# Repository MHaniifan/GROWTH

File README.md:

## GROWTH: Greenhouse Remote Operations With Temperature & Humidity

<div align="justify">
    Proyek ini bertujuan untuk mengembangkan sistem automasi cerdas berbasis Mikrokontroler AVR untuk Smart Farming, menggunakan komponen utama seperti Arduino Mega, sensor YL-69 dan DHT-11, serta pompa air dan kipas. Arduino Mega bertindak sebagai mikrokontroler utama yang mengontrol komunikasi antar sensor dan aktuator, memungkinkan pemantauan dan pengontrolan secara real-time. Sistem ini menggunakan Timer pada AVR untuk menjaga sinkronisasi waktu, dan Interrupt untuk menyalakan Pompa Air ketika kelembaban dibawah batas.
</div>

<div align="justify">
    Pompa Air akan menyala setiap jadwal penyiraman yang sudah ditentukan. Dimana jadwal penyiraman dan lama pompa menyala, diatur pada GUI pada Komputer yang terhubung ke Mikrokontroler menggunakan komunikasi UART. Untuk Kipas akan menyala setiap suhu telah melewati batas yang ditentukan, dimana batas suhunya dapat diatur pada GUI.
</div>

<div align="justify">
    Dengan menggunakan UART, seluruh data dari sensor-sensor ini dikirimkan ke Komputer. Memungkinkan petani untuk memantau penggunaan energi dan kondisi lingkungan secara langsung dari Komputer. Sistem ini dirancang untuk meningkatkan efisiensi energi, hasil produksi, serta dapat mengurangi kerugian dengan mengotomatiskan berbagai fungsi dan memberikan kendali yang lebih fleksibel.
</div>

## Supported By :
>- Dosen Pengampu : Akhmad Hendriawan ST., MT. (NIP.197501272002121003)
>- Mata kuliah : Mikrokontroler
>- Program Studi : Sarjana Terapan Teknik Elektronika
>- Politeknik Elektronika Negeri Surabaya<br> 

## Team Member :
|      NRP      |       Nama      |    Jobdesk    |   Github |
| :-----------:|:----------------:| :------------:| :-----:|
| 2123600007    | Muhammad Haniifan  | Project Manager       | [Haniifan](https://github.com/MHaniifan)
| 2123600011    | Monalisa Br. Sidauruk         |   Hardware Specialist | [Lisa](https://github.com/MonalisaSidauruk)
| 2123600015    | Fakhrihans Ardiyanto         |    UI/UX Designer      | [Rihan](https://github.com/FakhrihansArdiyanto)
| 2123600027    | Darda Drestanala                | 3D Designer | [Darda](https://github.com/dardadrestanala)
| 2123600029    | Aurora Putri Salsabillah Rofii               | PCB Designer     | [Aurora](https://github.com/aurorapsr)
| 2124640016    | Arif Ramadhan               | Programmer     |[Arif](https://github.com/arif-rmdhn)

##

## Daftar Isi
- [Deskripsi Project](https://github.com/MHaniifan/GROWTH#growth-greenhouse-remote-operations-with-temperaturehumidity)
- [Team Member](https://github.com/MHaniifan/GROWTH#team-member-)
- [Keunggulan](https://github.com/MHaniifan/GROWTH#keunggulan)
- [Desain Hardware](https://github.com/MHaniifan/GROWTH#desain-hardware)
- [Printed Circuit Board](https://github.com/MHaniifan/GROWTH#printed-circuit-board-pcb)
- [Program](https://github.com/MHaniifan/GROWTH#program)
- [Tampilan UI/UX](https://github.com/MHaniifan/GROWTH#tampilan-uiux)

## Keunggulan
- **Pemantauan Real-Time**: Mengukur perubahan kelembaban dan suhu dengan sensor secara terus - menerus.
- **Efisiensi dan Penghematan Biaya**: Mengurangi penggunaan listrik karena pompa dan kipas hanya dinyalakan ketika melewati batas normal tanaman.
- **Kendali Otomatis**: Menggunakan sensor untuk mengamati perubahan kondisi dan relay untuk mengaktifkan pompa dan kipas sehingga tidak dikontrol oleh manusia.
- **Meningkatkan Hasil Panen**: Mencegah tanaman kekeringan dan kepanasan sehingga dapat meningkatkan kondisi tanaman.

## Desain Hardware
Blok Diagram

Wiring Diagram

## Printed Circuit Board (PCB)
Skematik PCB

Desain PCB

## Desain 3D

## Flowchart Program

## Tampilan UI/UX

## Pengembangan Kedepannya
- Penambahan IoT untuk Pemantauan Jarak Jauh
- Penambahan RTC untuk Penjadwalan Penyiraman
- Penambahan Desain Casing yang Tahan Air
- Penambahan Baterai untuk Supply Darurat

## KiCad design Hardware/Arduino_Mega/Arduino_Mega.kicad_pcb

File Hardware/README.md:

## Desain Hardware
Blok Diagram

Wiring Diagram

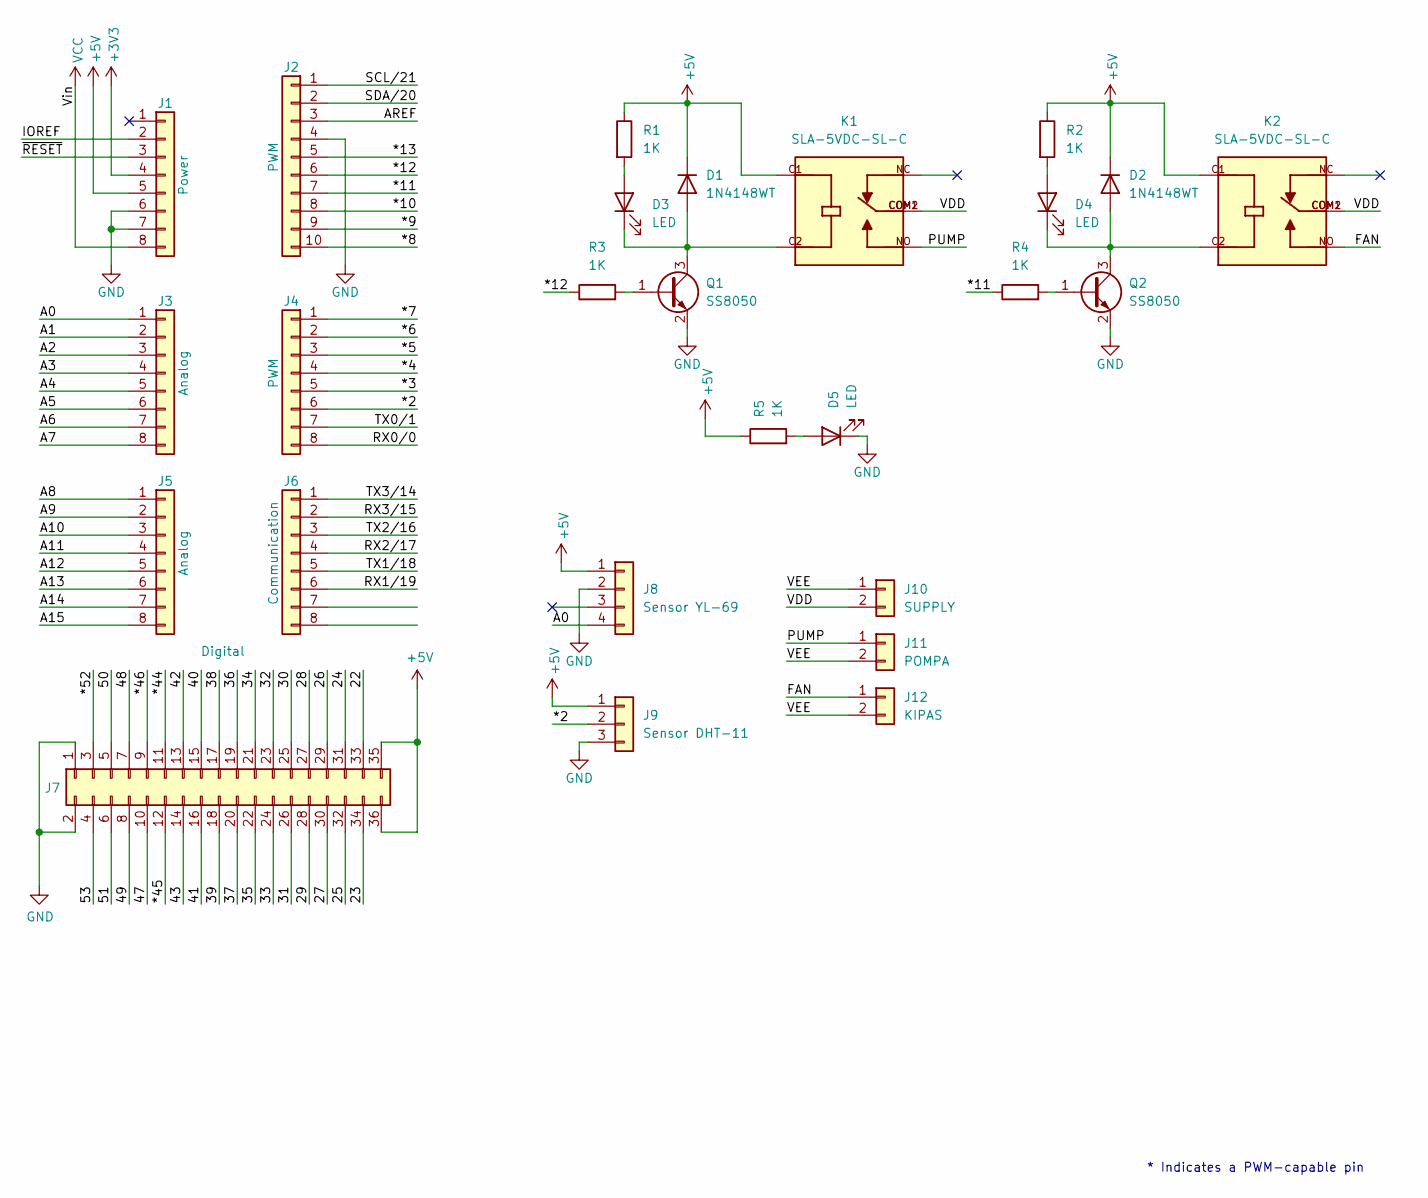
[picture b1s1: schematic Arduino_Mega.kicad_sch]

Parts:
D1, D2: 1N4148WT; D_SOD-523
D3, D4, D5: LED; LED_1206_3216Metric_Pad1.42x1.75mm_HandSolder
J1: Power; PinSocket_1x08_P2.54mm_Vertical
J2: PWM; PinSocket_1x10_P2.54mm_Vertical
J3, J5: Analog; PinSocket_1x08_P2.54mm_Vertical
J4: PWM; PinSocket_1x08_P2.54mm_Vertical
J6: Communication; PinSocket_1x08_P2.54mm_Vertical
J7: Digital; PinSocket_2x18_P2.54mm_Vertical
J8: Sensor YL-69; JST_XH_B4B-XH-A_1x04_P2.50mm_Vertical
J9: Sensor DHT-11; JST_XH_B3B-XH-A_1x03_P2.50mm_Vertical
J10: SUPPLY; TerminalBlock_Phoenix_MKDS-1,5-2-5.08_1x02_P5.08mm_Horizont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
J11: POMPA; TerminalBlock_Phoenix_MKDS-1,5-2-5.08_1x02_P5.08mm_Horizont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
J12: KIPAS; TerminalBlock_Phoenix_MKDS-1,5-2-5.08_1x02_P5.08mm_Horizont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
K1, K2: SLA-5VDC-SL-C; RELAY_SLA-12VDC-SL-C
Q1, Q2: SS8050; SOT-23
R1, R2, R3, R4, R5: 1K; R_0805_2012Metric_Pad1.20x1.40mm_HandSolder

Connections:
+3V3: J1.4
+5V: D1.1 (K), D2.1 (K), J1.5, J7.35, J7.36, J8.1, J9.1, K1.C1, K2.C1, R1.1, R2.1, R5.1
/22: J7.33
/23: J7.34
/24: J7.31
/25: J7.32
/26: J7.29
/27: J7.30
/28: J7.27
/29: J7.28
/30: J7.25
/31: J7.26
/32: J7.23
/33: J7.24
/34: J7.21
/35: J7.22
/36: J7.19
/37: J7.20
/38: J7.17
/39: J7.18
/40: J7.15
/41: J7.16
/42: J7.13
/43: J7.14
/47: J7.10
/48: J7.7
/49: J7.8
/50: J7.5
/51: J7.6
/53: J7.4
/*2: J4.6, J9.2
/*3: J4.5
/*4: J4.4
/*5: J4.3
/*6: J4.2
/*7: J4.1
/*8: J2.10
/*9: J2.9
/*10: J2.8
/*11: J2.7, R4.1
/*12: J2.6, R3.1
/*13: J2.5
/*44: J7.11
/*45: J7.12
/*46: J7.9
/*52: J7.3
/A0: J3.1, J8.4
/A1: J3.2
/A2: J3.3
/A3: J3.4
/A4: J3.5
/A5: J3.6
/A6: J3.7
/A7: J3.8
/A8: J5.1
/A9: J5.2
/A10: J5.3
/A11: J5.4
/A12: J5.5
/A13: J5.6
/A14: J5.7
/A15: J5.8
/AREF: J2.3
/FAN: J12.1, K2.NO
/IOREF: J1.2
/PUMP: J11.1, K1.NO
/RX0/0: J4.8
/RX1/19: J6.6
/RX2/17: J6.4
/RX3/15: J6.2
/SCL/21: J2.1
/SDA/20: J2.2
/TX0/1: J4.7
/TX1/18: J6.5
/TX2/16: J6.3
/TX3/14: J6.1
/VDD: J10.2, K1.COM1, K1.COM2, K2.COM1, K2.COM2
/VEE: J10.1, J11.2, J12.2
/~RESET: J1.3
GND: D5.1 (K), J1.6, J1.7, J2.4, J7.1, J7.2, J8.2, J9.3, Q1.2 (E), Q2.2 (E)
unnamed: D1.2 (A), D3.1 (K), K1.C2, Q1.3 (C)
unnamed: D2.2 (A), D4.1 (K), K2.C2, Q2.3 (C)
unnamed: D3.2 (A), R1.2
unnamed: D4.2 (A), R2.2
unnamed: D5.2 (A), R5.2
unnamed: Q1.1 (B), R3.2
unnamed: Q2.1 (B), R4.2
VCC: J1.8

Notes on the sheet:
* Indicates a PWM-capable pin

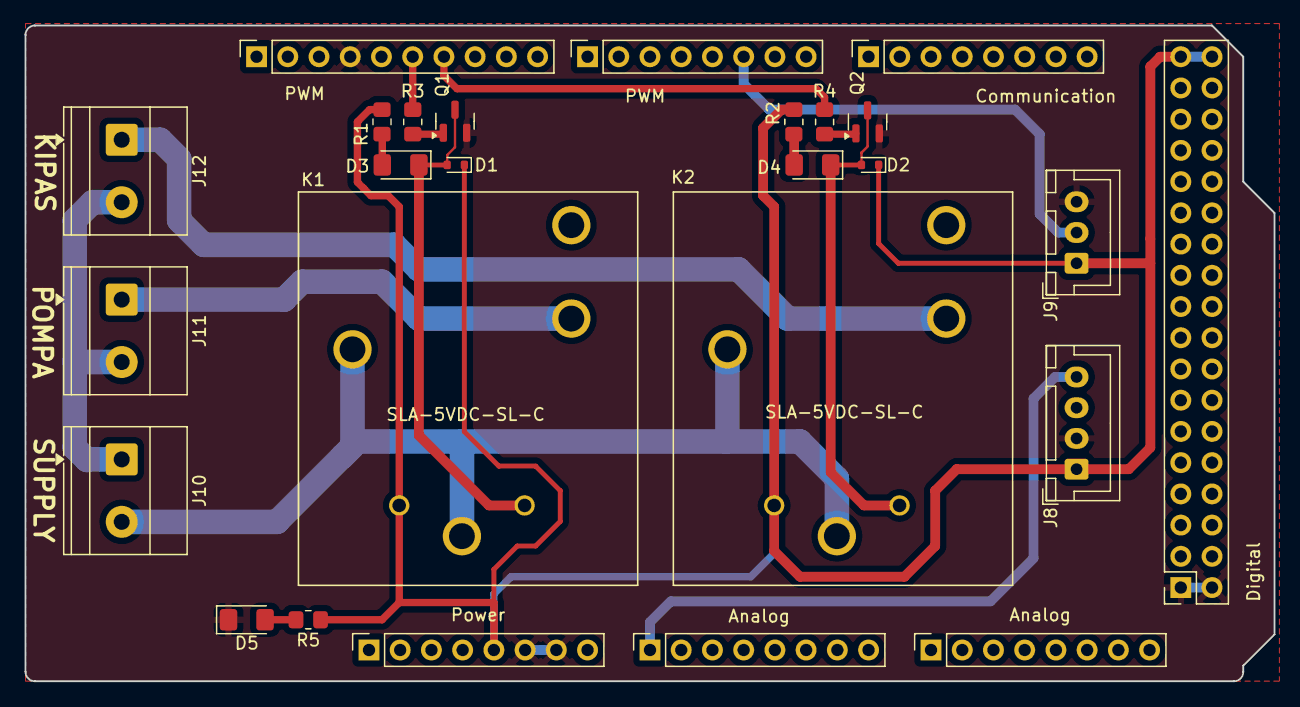
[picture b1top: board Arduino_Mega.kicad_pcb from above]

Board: 2 copper layers, 101.6 x 53.3 mm, 26 parts (0 on the bottom side), 17 nets.

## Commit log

2025-04-18 Delete
2025-04-18 Update Folder
2025-04-28 Create Assets
    Add folder
2025-04-28 Create ....
2025-04-28 Add Folder
2025-05-06 Add Files
2025-05-19 Rename Folder
2025-05-19 Create New Folder
2025-05-19 Edit Files
2025-05-20 Update Program 20/05/2025
2025-05-30 update program
2025-06-02 Add Fuxa Program
2025-06-02 Edit README.md
2025-06-02 edit main.cpp
2025-06-02 Rename Files
2025-06-02 Add README.md
